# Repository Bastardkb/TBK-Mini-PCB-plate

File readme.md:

# TBK Mini PCB - plate

Flexible PCB made for the TBK Mini.

With per-key RGB.

This repository contains all files necessary to order a PCB.

If you want to modify the design files, the Kicad sources are included.
If you just want to order the PCBs, check out the Release section which contain the gerber files.

## How to order

Order with a 0.6mm or 0.8mm PCB thickness

## License

Licensed under CC BY-NC-SA 4.0
Copyright Quentin Lebastard 2021

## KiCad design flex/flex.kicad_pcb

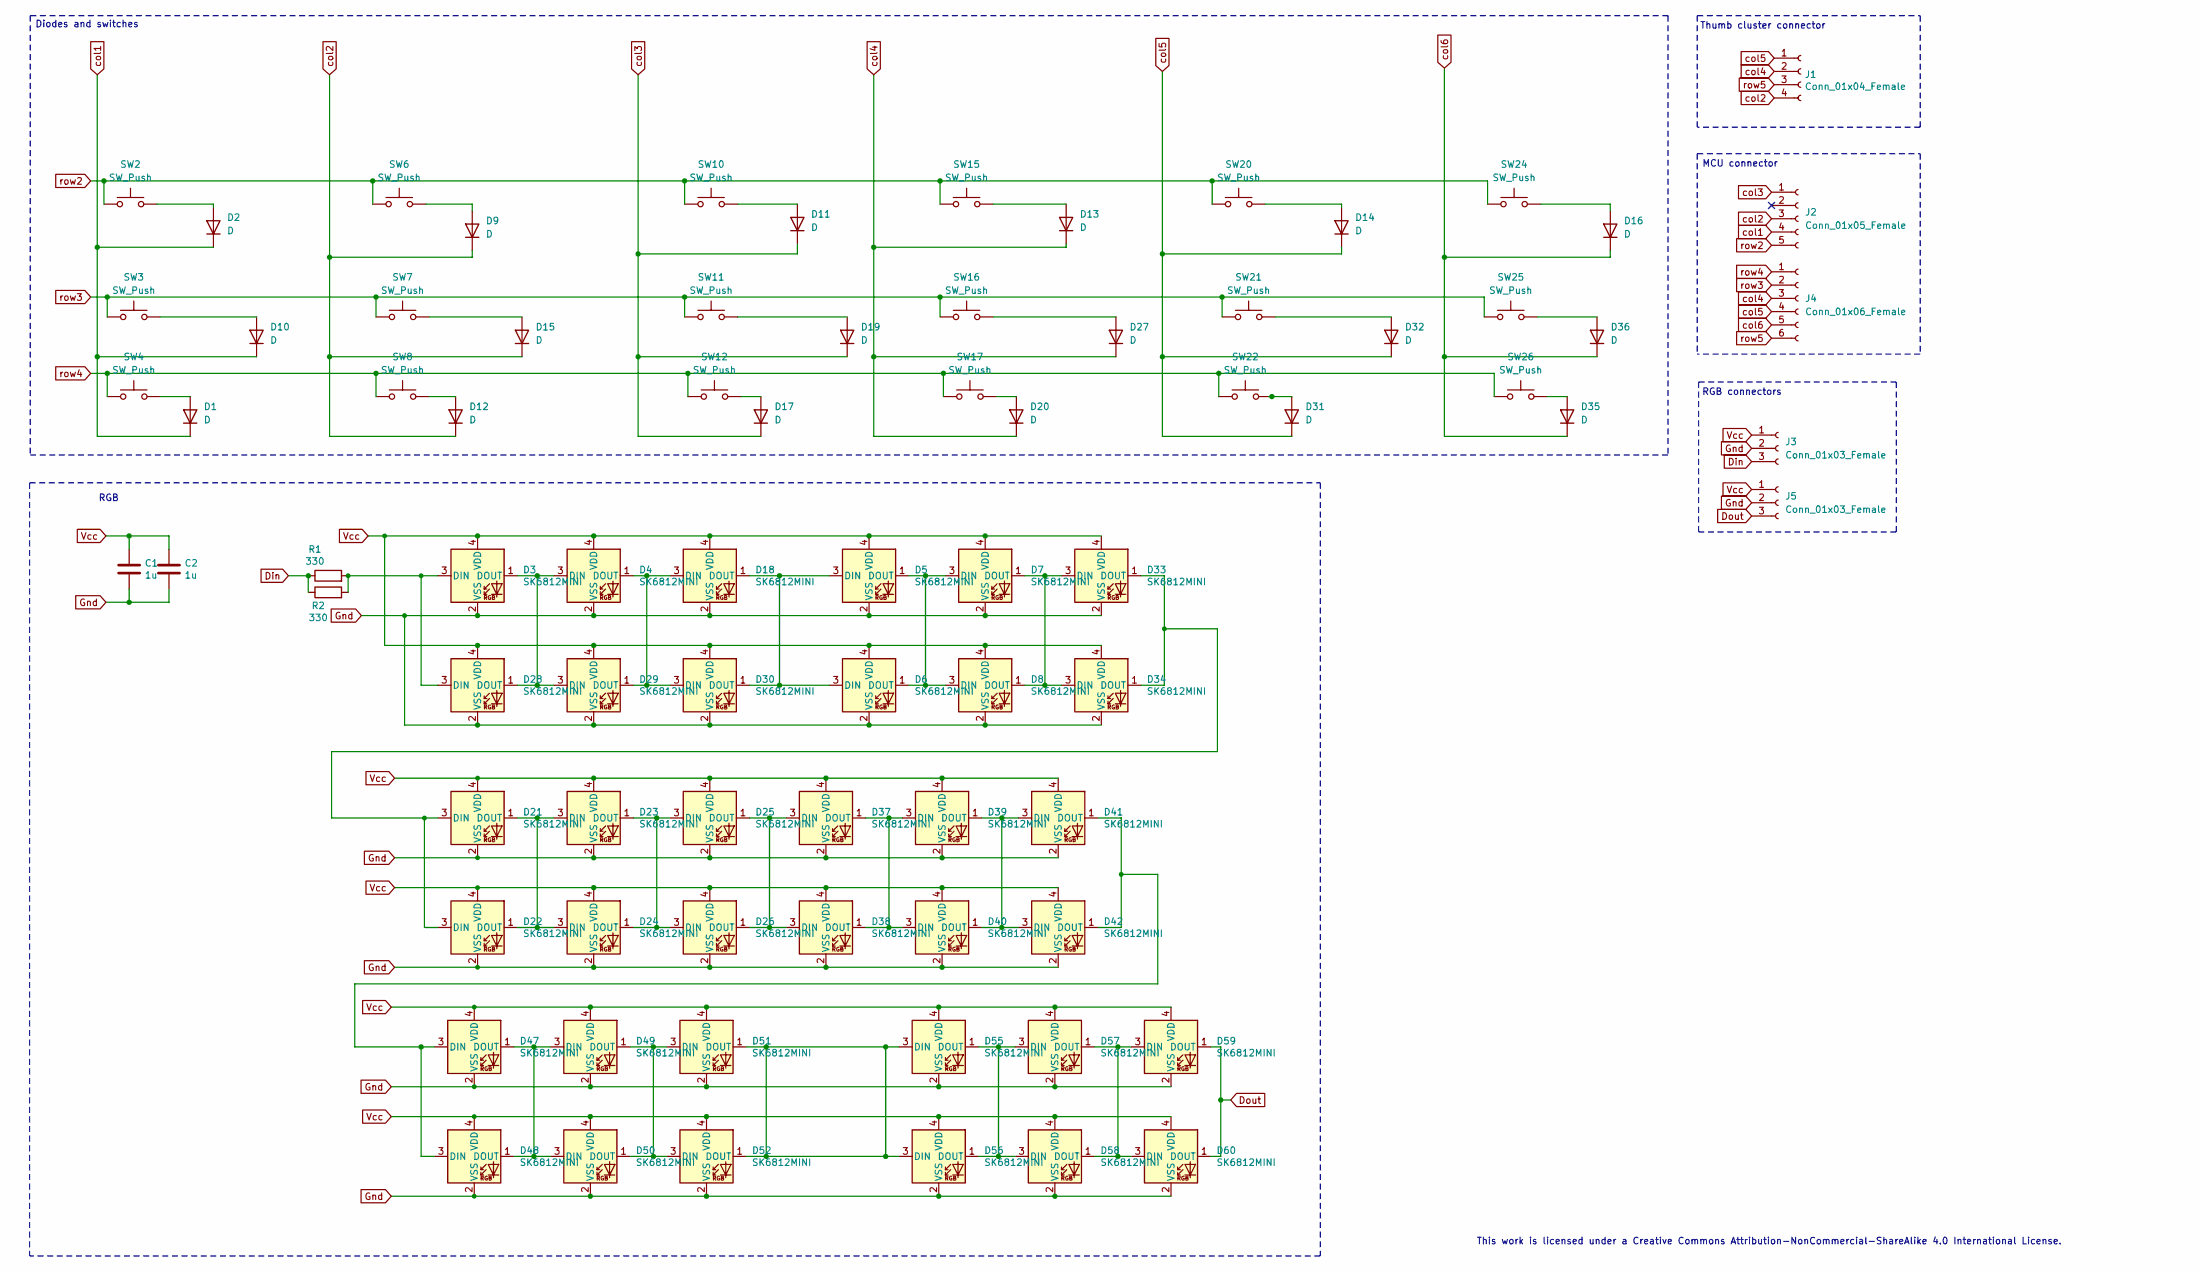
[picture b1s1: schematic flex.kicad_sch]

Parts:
C1, C2: 1u; C_1206_3216Metric_Pad1.42x1.75mm_HandSolder
D1, D2, D9, D10, D11, D12, D13, D14, D15, D16, D17, D19, D20, D27, D31, D32, D35, D36: D; Diode_TH_SOD123
D3, D4, D5, D7, D18, D21, D23, D25, D33, D37, D39, D41, D47, D49, D51, D55, D57, D59: SK6812MINI; SK6812_mini_e_corners
D6, D8, D22, D24, D26, D28, D29, D30, D34, D38, D40, D42, D48, D50, D52, D56, D58, D60: SK6812MINI; SK6812_mini_e_corners_NOEDGECUTS
J1: Conn_01x04_Female; PinHeader_1x04_P2.54mm_Vertical
J2: Conn_01x05_Female; PinHeader_1x05_P2.54mm_Vertical
J3, J5: Conn_01x03_Female; PinHeader_1x03_P2.54mm_Vertical
J4: Conn_01x06_Female; PinHeader_1x06_P2.54mm_Vertical
R1, R2: 330; R_1206_3216Metric_Pad1.42x1.75mm_HandSolder
SW2, SW3, SW4, SW6, SW7, SW8, SW10, SW11, SW12, SW15, SW16, SW17, SW20, SW21, SW22, SW24, SW25, SW26: SW_Push; SW_MX_reversible

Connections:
Din: J3.3, R1.1, R2.1
Dout: D59.1 (DOUT), D60.1 (DOUT), J5.3
Gnd: C1.2, C2.2, D3.2 (VSS), D4.2 (VSS), D5.2 (VSS), D6.2 (VSS), D7.2 (VSS), D8.2 (VSS), D18.2 (VSS), D21.2 (VSS), D22.2 (VSS), D23.2 (VSS), D24.2 (VSS), D25.2 (VSS), D26.2 (VSS), D28.2 (VSS), D29.2 (VSS), D30.2 (VSS), D33.2 (VSS), D34.2 (VSS), D37.2 (VSS), D38.2 (VSS), D39.2 (VSS), D40.2 (VSS), D41.2 (VSS), D42.2 (VSS), D47.2 (VSS), D48.2 (VSS), D49.2 (VSS), D50.2 (VSS), D51.2 (VSS), D52.2 (VSS), D55.2 (VSS), D56.2 (VSS), D57.2 (VSS), D58.2 (VSS), D59.2 (VSS), D60.2 (VSS), J3.2, J5.2
unnamed: D1.2 (A), SW4.2
unnamed: D2.2 (A), SW2.2
unnamed: D5.1 (DOUT), D6.1 (DOUT), D7.3 (DIN), D8.3 (DIN)
unnamed: D9.2 (A), SW6.2
unnamed: D10.2 (A), SW3.2
unnamed: D11.2 (A), SW10.2
unnamed: D12.2 (A), SW8.2
unnamed: D13.2 (A), SW15.2
unnamed: D14.2 (A), SW20.2
unnamed: D15.2 (A), SW7.2
unnamed: D16.2 (A), SW24.2
unnamed: D17.2 (A), SW12.2
unnamed: D5.3 (DIN), D6.3 (DIN), D18.1 (DOUT), D30.1 (DOUT)
unnamed: D4.1 (DOUT), D18.3 (DIN), D29.1 (DOUT), D30.3 (DIN)
unnamed: D19.2 (A), SW11.2
unnamed: D20.2 (A), SW17.2
unnamed: D21.1 (DOUT), D22.1 (DOUT), D23.3 (DIN), D24.3 (DIN)
unnamed: D21.3 (DIN), D22.3 (DIN), D33.1 (DOUT), D34.1 (DOUT)
unnamed: D23.1 (DOUT), D24.1 (DOUT), D25.3 (DIN), D26.3 (DIN)
unnamed: D25.1 (DOUT), D26.1 (DOUT), D37.3 (DIN), D38.3 (DIN)
unnamed: D27.2 (A), SW16.2
unnamed: D3.1 (DOUT), D4.3 (DIN), D28.1 (DOUT), D29.3 (DIN)
unnamed: D3.3 (DIN), D28.3 (DIN), R1.2, R2.2
unnamed: D31.2 (A), SW22.2
unnamed: D32.2 (A), SW21.2
unnamed: D7.1 (DOUT), D8.1 (DOUT), D33.3 (DIN), D34.3 (DIN)
unnamed: D35.2 (A), SW26.2
unnamed: D36.2 (A), SW25.2
unnamed: D37.1 (DOUT), D38.1 (DOUT), D39.3 (DIN), D40.3 (DIN)
unnamed: D39.1 (DOUT), D40.1 (DOUT), D41.3 (DIN), D42.3 (DIN)
unnamed: D41.1 (DOUT), D42.1 (DOUT), D47.3 (DIN), D48.3 (DIN)
unnamed: D47.1 (DOUT), D48.1 (DOUT), D49.3 (DIN), D50.3 (DIN)
unnamed: D49.1 (DOUT), D50.1 (DOUT), D51.3 (DIN), D52.3 (DIN)
unnamed: D51.1 (DOUT), D52.1 (DOUT), D55.3 (DIN), D56.3 (DIN)
unnamed: D55.1 (DOUT), D56.1 (DOUT), D57.3 (DIN), D58.3 (DIN)
unnamed: D57.1 (DOUT), D58.1 (DOUT), D59.3 (DIN), D60.3 (DIN)
Vcc: C1.1, C2.1, D3.4 (VDD), D4.4 (VDD), D5.4 (VDD), D6.4 (VDD), D7.4 (VDD), D8.4 (VDD), D18.4 (VDD), D21.4 (VDD), D22.4 (VDD), D23.4 (VDD), D24.4 (VDD), D25.4 (VDD), D26.4 (VDD), D28.4 (VDD), D29.4 (VDD), D30.4 (VDD), D33.4 (VDD), D34.4 (VDD), D37.4 (VDD), D38.4 (VDD), D39.4 (VDD), D40.4 (VDD), D41.4 (VDD), D42.4 (VDD), D47.4 (VDD), D48.4 (VDD), D49.4 (VDD), D50.4 (VDD), D51.4 (VDD), D52.4 (VDD), D55.4 (VDD), D56.4 (VDD), D57.4 (VDD), D58.4 (VDD), D59.4 (VDD), D60.4 (VDD), J3.1, J5.1
col1: D1.1 (K), D2.1 (K), D10.1 (K), J2.4
col2: D9.1 (K), D12.1 (K), D15.1 (K), J1.4, J2.3
col3: D11.1 (K), D17.1 (K), D19.1 (K), J2.1
col4: D13.1 (K), D20.1 (K), D27.1 (K), J1.2, J4.3
col5: D14.1 (K), D31.1 (K), D32.1 (K), J1.1, J4.4
col6: D16.1 (K), D35.1 (K), D36.1 (K), J4.5
row2: J2.5, SW2.1, SW6.1, SW10.1, SW15.1, SW20.1, SW24.1
row3: J4.2, SW3.1, SW7.1, SW11.1, SW16.1, SW21.1, SW25.1
row4: J4.1, SW4.1, SW8.1, SW12.1, SW17.1, SW22.1, SW26.1
row5: J1.3, J4.6

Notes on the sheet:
RGB
Diodes and switches
Thumb cluster connector
RGB connectors
MCU connector
This work is licensed under a Creative Commons Attribution-NonCommercial-ShareAlike 4.0 International License.

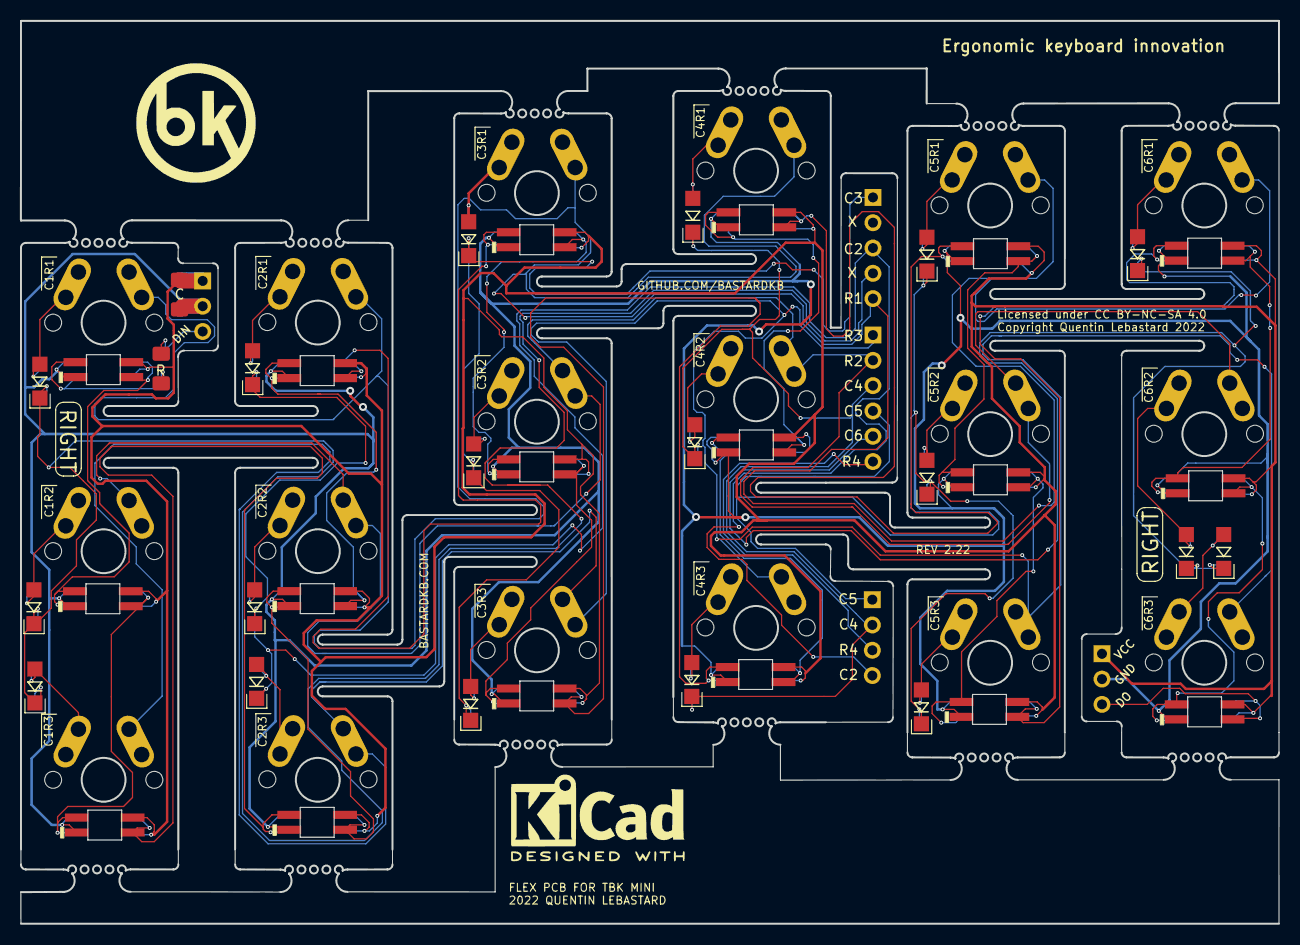
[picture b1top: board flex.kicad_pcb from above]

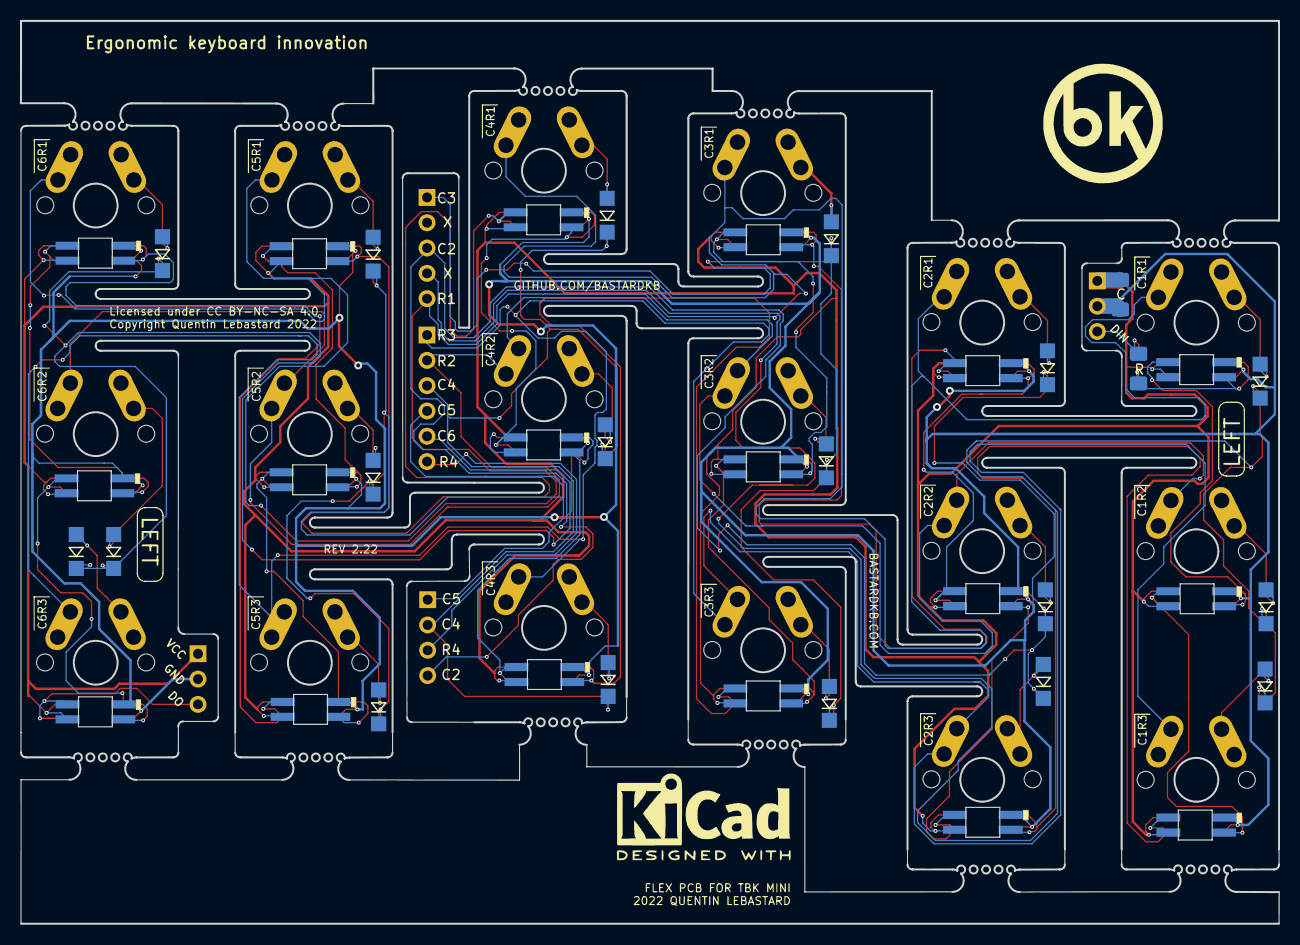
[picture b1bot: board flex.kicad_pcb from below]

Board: 2 copper layers, 126.3 x 90.6 mm, 81 parts (38 on the bottom side), 50 nets.

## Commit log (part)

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2022-01-14 add stuff
2022-01-19 add pic
2024-06-27 edge cuts
2024-06-28 new pcba/handsolder footprint
2024-06-28 place components
2024-06-28 routing
2024-07-02 bigger pin holes
2024-07-02 bigger switch holes
2024-07-17 rgb leds gnd silkscreen
2024-07-26 diode routing

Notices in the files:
flex/flex.kicad_pcb:
Copyright Quentin Lebastard 2022
